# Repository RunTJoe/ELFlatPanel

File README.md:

# DIY Electroluminescence Flatfield Panel

## Overview

Features:

- Software controlled brightness

- Motorized telescope cover

- "Alnitak Generic Commands" compatible protocol

- 3D printed enclosure

The panel is designed for my 120mm refractor. I have mounted a 160mm EL panel into a 3D printed telescope cover. A servo motor opens and closes the cover.

Brightness and open/close operation are controlled by software using an "Alnitak Generic Commands" compatible protocol. This protocol is supported by several imaging software, I have tested operation in depth with imaging software "[Voyager](https://software.starkeeper.it/)" and briefly with "[N.I.N.A.](https://nighttime-imaging.eu/)".

Meanwhile I have successfully tested the panel for a whole night of unattended operation with temperatures below 0°C/ 32°F. During this night I shot multiple targets with different rotator angles and got the fitting flats for each rotator position. The imaging software automatically determined the correct brightness for luminance and narrowband filters and a fixed exposure time to fit my flatdark library.

## Panel

The panel is a cheap 160mm EL panel from Aliexpress. The controller is designed to be connected to a 12V inverter.

## Enclosure/Mounting

The whole enclosure, servo motor attachment and telescope "tube ring" are 3D printed. I have added a laser cut acrylic diffusor plate, although I don’t know whether this necessary.

## Controller

The controller is based on an Arduino Nano. The servo is controlled directly by a PWM pin of the Arduino. The inverter of the EL panel is a 12V inverter and the brightness is dimmed by reducing the inverter input voltage. For that purpose I have used an external DAC MCP4725 (the Arduino analog outputs are just PWM digital outputs) and translated the 0-5V output of this DAC via an OpAmp and a darlington transistor to 0-10V.

I have designed a PCB (using KiCAD) to fit into a very compact project box (8x5x2cm) which remains fixed on the refractor while it is stored in the telescope case. 

By default, the Arduino resets on each connect by the USB serial port. By shorting JP1 with a jumper this reset can be disabled. This is useful if the controller is connected to software with tight timeouts. You must remove the jumper if you want to update the Arduino firmware.

Front and back plates of the box are aluminum "PCBs" produced at the same PCB manufacturer ([JLCPCB](https://jlcpcb.com/)).

**Note**: The manufacturer JLCPCB adds by default an order number on each PCB. If you spend \$1.50 more, you can choose an [option to get the PCB without the order number](https://support.jlcpcb.com/article/28-how-to-put-jlc-production-id-at-a-specified-area-on-the-pcb).

The mini-USB connector of the Arduino Nano is routed to a more reliable USB-B connector. Supply voltage is the usual 12V, a DC/DC converter module on the PCB provides 5V power for the servo motor. I have bought the Arduino and DC/DC converter as complete modules, all other components are just hand soldered on my own PCB (the red PCB on the image). 

**Note**: The DC/DC converter has adjustable output voltage and must be adjusted to a voltage fitting the servo (usually 5V).

## Servo

The servo is an RDS3115 with a range of 270 degrees. With my servo attachment about 225 degrees can be used.

The exact PWM values for opening and closing angles can be adjusted in the firmware:

```
const int SERVOPOS_CLOSE = 3;        // servo position for closed cover
const int SERVOPOS_OPEN = 158;       // servo position for open cover 
```

For easy evaluation of the proper settings, I have extended the Alnitak protocol with an additional command to set any PWM value:

Set ddd as servo PWM value:

\>Zddd*CR*

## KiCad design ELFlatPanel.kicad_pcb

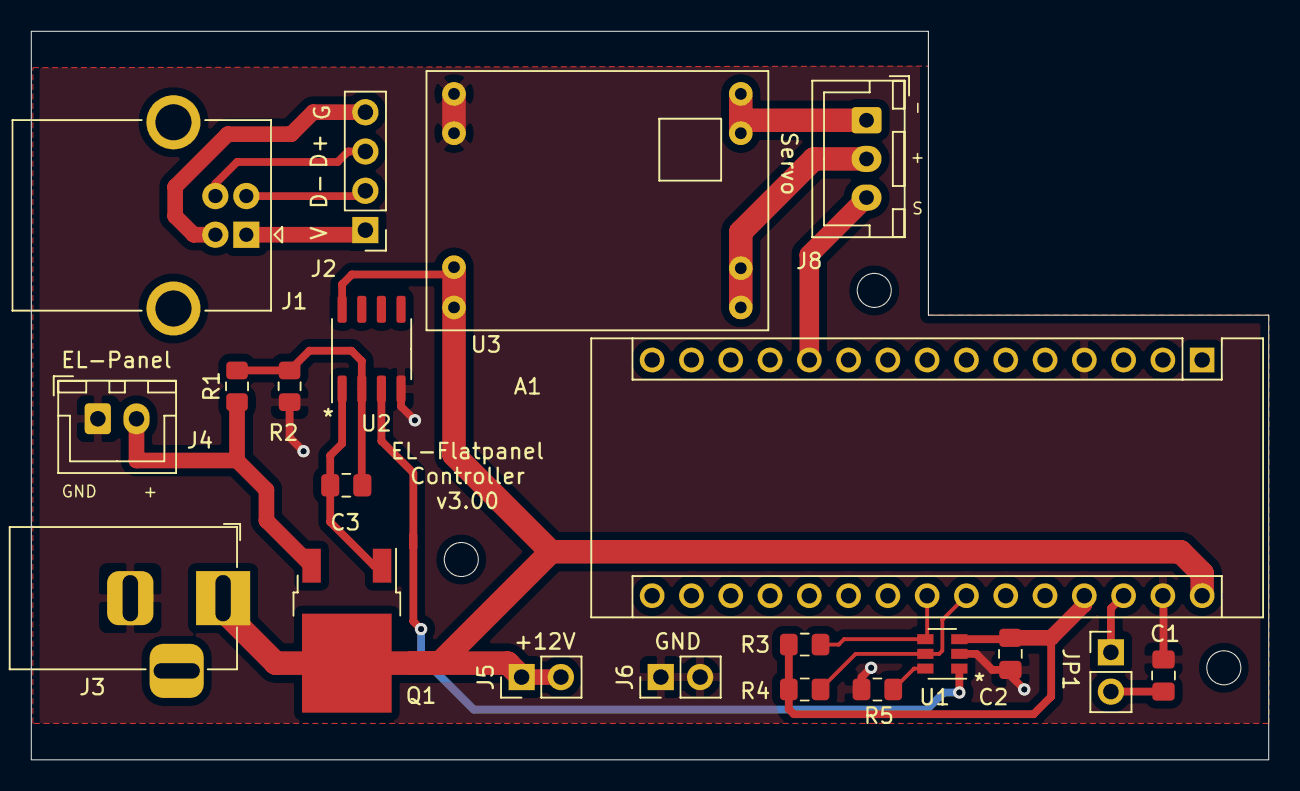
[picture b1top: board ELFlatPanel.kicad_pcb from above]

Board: 2 copper layers, 80.0 x 47.1 mm, 21 parts (0 on the bottom side), 19 nets.

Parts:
A1: Arduino_Nano_v3.x; Arduino_Nano
C1: 10uF; C_0805_2012Metric_Pad1.18x1.45mm_HandSolder
C2: 0.1uF; C_0805_2012Metric_Pad1.18x1.45mm_HandSolder
C3: 100pF; C_0805_2012Metric_Pad1.18x1.45mm_HandSolder
J1: USB_B; USB_B_OST_USB-B1HSxx_Horizontal
J2: Conn_01x04; PinHeader_1x04_P2.54mm_Vertical
J3: Barrel_Jack_Switch; BarrelJack_Horizontal
J4: Conn_01x02; JST_XH_B2B-XH-A_1x02_P2.50mm_Vertical
J5, J6: Conn_01x02; PinHeader_1x02_P2.54mm_Vertical
J8: Conn_01x03; JST_XH_B3B-XH-A_1x03_P2.50mm_Vertical
JP1: Jumper; PinHeader_1x02_P2.54mm_Vertical
Q1: MJD122; TO-252-2
R1, R2, R3, R4: 4k7; R_0805_2012Metric_Pad1.15x1.40mm_HandSolder
R5: 10k; R_0805_2012Metric_Pad1.15x1.40mm_HandSolder
U1: MCP4725A0T-ECH; SOT-23-6
U2: LM358; SO-8_3.9x4.9mm_P1.27mm
U3: MP1584ModuleDcDc; MP1584_DCDC_Module

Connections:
+5V: A1.27, C2.2, R3.2, R4.1, U1.3
+12V: A1.30, J3.1, J5.1, J5.2, Q1.2, U2.8, U3.1, U3.2
GND: A1.4, A1.29, C1.2, C2.1, J3.2, J4.1, J6.1, J6.2, R2.2, R5.2, U1.2, U2.4, U3.3, U3.4
unnamed: A1.23, R3.1, U1.4
unnamed: A1.24, R4.2, U1.5
unnamed: A1.28, JP1.1
unnamed: C1.1, JP1.2
unnamed: C3.1, Q1.1, U2.1
unnamed: C3.2, R1.2, R2.1, U2.2
unnamed: J1.1, J2.1
unnamed: J1.2, J2.2
unnamed: J1.3, J2.3
unnamed: J1.4, J2.4
unnamed: J8.1, U3.5, U3.6
unnamed: J8.2, U3.7, U3.8
unnamed: R5.1, U1.6
unnamed: U1.1, U2.3
ServoOut: A1.11, J8.3
Vout: J4.2, Q1.3, R1.1

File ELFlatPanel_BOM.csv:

"Ref","Qnty","Value","Cmp name","Footprint","Description","Vendor"
"A1, ","1","Arduino_Nano_v3.x","Arduino_Nano_v3.x","Module:Arduino_Nano","Arduino Nano v3.x",""
"C1, ","1","10uF","CP","Capacitor_SMD:C_0805_2012Metric_Pad1.18x1.45mm_HandSolder","Polarized capacitor",""
"C2, ","1","0.1uF","C","Capacitor_SMD:C_0805_2012Metric_Pad1.18x1.45mm_HandSolder","Unpolarized capacitor",""
"C3, ","1","100pF","C","Capacitor_SMD:C_0805_2012Metric_Pad1.18x1.45mm_HandSolder","Unpolarized capacitor",""
"J1, ","1","USB_B","USB_B","Connector_USB:USB_B_OST_USB-B1HSxx_Horizontal","USB Type B connector",""
"J2, ","1","Conn_01x04","Conn_01x04","Connector_PinHeader_2.54mm:PinHeader_1x04_P2.54mm_Vertical","Generic connector, single row, 01x04, script generated (kicad-library-utils/schlib/autogen/connector/)",""
"J3, ","1","Barrel_Jack_Switch","Barrel_Jack_Switch","Connector_BarrelJack:BarrelJack_Horizontal","DC Barrel Jack with an internal switch",""
"J4, ","1","Conn_01x02","Conn_01x02","Connector_JST:JST_XH_B2B-XH-A_1x02_P2.50mm_Vertical","Generic connector, single row, 01x02, script generated (kicad-library-utils/schlib/autogen/connector/)",""
"J5, J6, ","2","Conn_01x02","Conn_01x02","Connector_PinHeader_2.54mm:PinHeader_1x02_P2.54mm_Vertical","Generic connector, single row, 01x02, script generated (kicad-library-utils/schlib/autogen/connector/)",""
"J8, ","1","Conn_01x03","Conn_01x03","Connector_JST:JST_XH_B3B-XH-A_1x03_P2.50mm_Vertical","Generic connector, single row, 01x03, script generated (kicad-library-utils/schlib/autogen/connector/)",""
"JP1, ","1","Jumper","Jumper","Connector_PinHeader_2.54mm:PinHeader_1x02_P2.54mm_Vertical","Jumper, normally closed",""
"Q1, ","1","MJD122","TIP122","Package_TO_SOT_SMD:TO-252-2","5A Ic, 100V Vce, Silicon Darlington Power NPN Transistor, TO-220",""
"R1, R2, R3, R4, ","4","4k7","R","Resistor_SMD:R_0805_2012Metric_Pad1.15x1.40mm_HandSolder","Resistor",""
"R5, ","1","10k","R","Resistor_SMD:R_0805_2012Metric_Pad1.15x1.40mm_HandSolder","Resistor",""
"U1, ","1","MCP4725A0T-ECH","MCP4725xxx-xCH","Package_TO_SOT_SMD:SOT-23-6","12-bit Digital-to-Analog Converter, integrated EEPROM, I2C interface, SOT-23-6",""
"U2, ","1","LM358","LM358","Package_SO:SO-8_3.9x4.9mm_P1.27mm","Low-Power, Dual Operational Amplifiers, DIP-8/SOIC-8/TO-99-8",""
"U3, ","1","MP1584ModuleDcDc","MP1584ModuleDcDc","ELFlatPanel:MP1584_DCDC_Module","",""

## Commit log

2022-02-13 Fixed link to images
2022-02-14 Updated servo section
2022-02-17 Added front and back panel files
2022-02-17 Added .svg file for DiffusorPlate
2022-02-17 Modified .svg file for DiffusorPlate
